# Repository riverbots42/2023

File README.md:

# 2023

# Introduction

Clearinghouse repository for all code and random files related to the Riverbot team's 2023 robot stuff.

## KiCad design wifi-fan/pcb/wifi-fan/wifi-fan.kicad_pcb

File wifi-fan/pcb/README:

Files in this directory:

600px-OPiZero_pinout.jpg - The pinout of the OrangePi Zero and what each pin is on the headers.
opi-zero-gpio-pins-768x716.png - The GPIO name (that the board knows) mapped to the one that Linux knows about.
winning-amp.jpg - The audio amplifier design I went with.
winning-pcb-rendered.jpg - The final PCB that I ordered from PCBWay (in glorious 3D).
winning-pcb-schematic.jpg - The final PCB that I ordered from PCBWay (in schematic format).

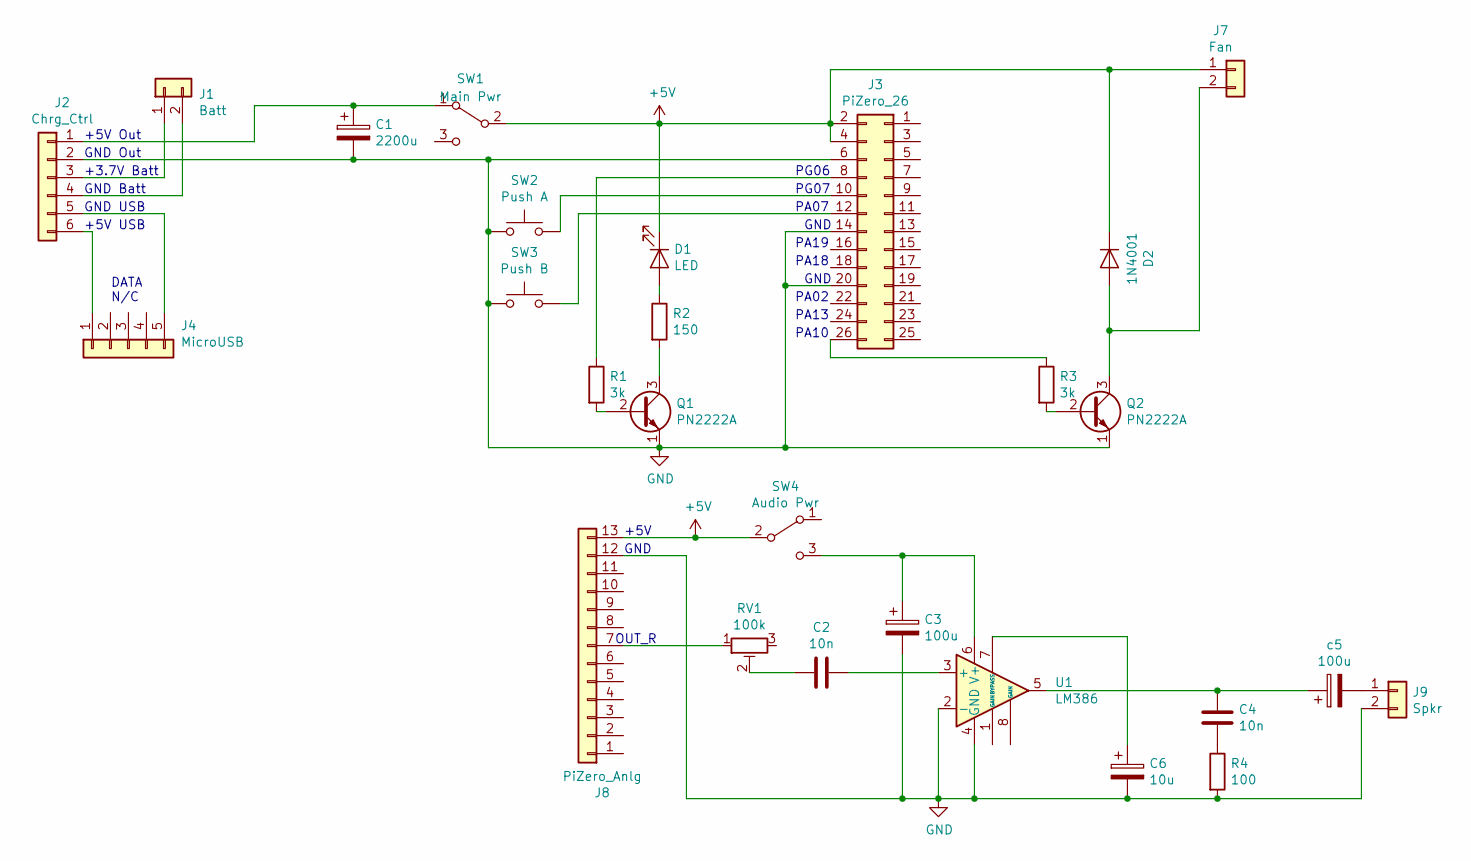
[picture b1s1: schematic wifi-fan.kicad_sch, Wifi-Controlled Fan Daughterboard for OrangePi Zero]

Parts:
C1: 2200u; CP_Radial_D10.0mm_P2.50mm
C2, C4: 10n; C_Disc_D5.0mm_W2.5mm_P2.50mm
C3: 100u; CP_Radial_D10.0mm_P2.50mm
C6: 10u; CP_Radial_D7.5mm_P2.50mm
D1: LED; LED_D5.0mm
D2: 1N4001; D_DO-41_SOD81_P10.16mm_Horizontal
J1: Batt; PinHeader_1x02_P2.54mm_Vertical
J2: Chrg_Ctrl; PinHeader_1x06_P2.54mm_Vertical
J3: PiZero_26; PinHeader_2x13_P2.54mm_Vertical
J4: MicroUSB; PinHeader_1x05_P2.54mm_Vertical
J7: Fan; PinHeader_1x02_P2.54mm_Vertical
J8: PiZero_Anlg; PinHeader_1x13_P2.54mm_Vertical
J9: Spkr; PinHeader_1x02_P2.54mm_Vertical
Q1, Q2: PN2222A; TO-92_Inline
R1, R3: 3k; R_Axial_DIN0207_L6.3mm_D2.5mm_P7.62mm_Horizontal
R2: 150; R_Axial_DIN0207_L6.3mm_D2.5mm_P7.62mm_Horizontal
R4: 100; R_Axial_DIN0207_L6.3mm_D2.5mm_P7.62mm_Horizontal
RV1: 100k; Potentiometer_Runtron_RM-065_Vertical
SW1: Main Pwr; SS12D00G3
SW2: Push A; SW_PUSH_6mm
SW3: Push B; SW_PUSH_6mm
SW4: Audio Pwr; SS12D00G3
U1: LM386; DIP-8_W7.62mm
c5: 100u; CP_Radial_D10.0mm_P2.50mm

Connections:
+5V: D1.1 (K), D2.1 (K), J3.2, J3.4, J7.1, J8.13, SW1.2 (B), SW4.2 (B); also elsewhere on the board
GND: C1.2, C3.2, C6.2, J2.2, J3.6, J3.14, J3.20, J8.12, J9.2, Q1.1 (E), Q2.1 (E), R4.2, SW2.1, SW3.1, U1.2 (-), U1.4 (GND)
unnamed 2: C1.1, J2.1, SW1.1 (A); also elsewhere on the board
unnamed: C2.1, RV1.2
unnamed: C2.2, U1.3 (+)
unnamed 5: C3.1, SW4.3 (C), U1.6 (V+); also elsewhere on the board
unnamed: C4.1, U1.5, c5.1
unnamed: C4.2, R4.1
unnamed: C6.1, U1.7 (BYPASS)
unnamed: D1.2 (A), R2.1
unnamed: D2.2 (A), J7.2, Q2.3 (C)
unnamed: J1.1, J2.3
unnamed: J1.2, J2.4
unnamed: J2.5, J4.5
unnamed: J2.6, J4.1
unnamed: J3.8, R1.1
unnamed: J3.10, SW2.2
unnamed: J3.12, SW3.2
unnamed: J3.26, R3.1
unnamed: J8.7, RV1.1
unnamed: J9.1, c5.2
unnamed: Q1.2 (B), R1.2
unnamed: Q1.3 (C), R2.2
unnamed: Q2.2 (B), R3.2

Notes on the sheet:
PA07
DATA N/C
GND
+3.7V Batt
PA13
PG07
+5V
+5V USB
GND Batt
GND Out
PA10
PA02
PA19
GND USB
OUT_R
+5V Out
PG06
PA18

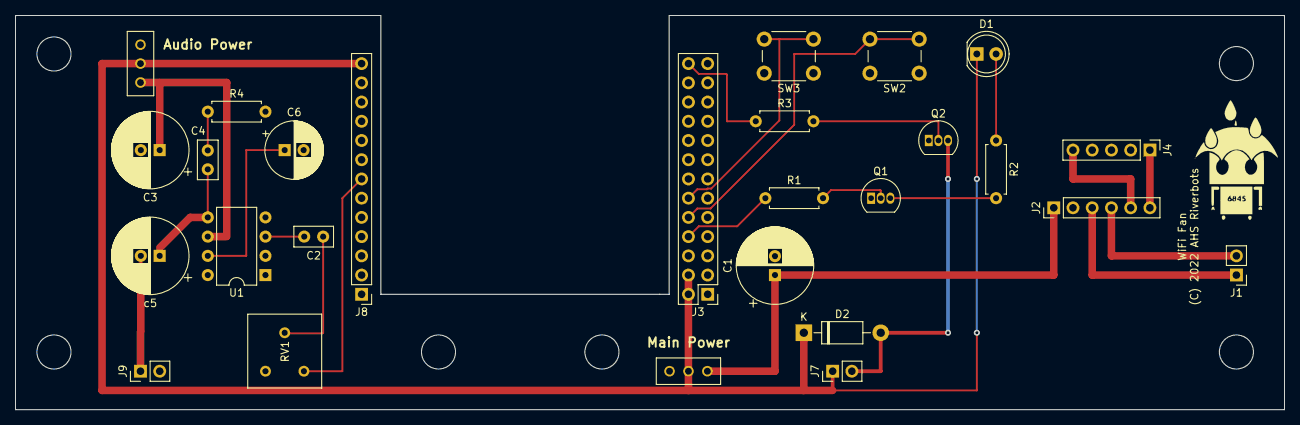
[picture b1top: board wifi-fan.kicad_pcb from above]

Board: 2 copper layers, 167.6 x 52.1 mm, 27 parts (0 on the bottom side), 24 nets.

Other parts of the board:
Audio Power: Audio Pwr; SS12D00G3
Main Power: Main Pwr; SS12D00G3

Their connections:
+5V: Audio Power.2, Main Power.2; also elsewhere on the board
unnamed 2: Main Power.1; also elsewhere on the board
unnamed 5: Audio Power.3; also elsewhere on the board

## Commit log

2022-11-03 Initial commit.
2022-11-05 Initial commit of the schematics.
2022-11-13 Add graphics.
2022-11-13 Updated to the version of the PCB BJ ordered.
2022-12-15 Initial riverbian release.
2023-01-07 Add 2023 template code from wpilib.
2023-01-07 Add beginning dox for install/download.
2023-01-08 Add test message.
2023-01-11 This is a test to see if I can commit changes
2023-01-12 hi there
2023-01-13 Fixed it.
2023-01-13 i fixed world peas
2023-01-14 Copied 2022 code for testing (On correct account)
2023-01-14 Altered 2022 code
2023-01-15 Add CTR dependencies.
2023-01-19 I've tried this
2023-01-19 please stop
2023-01-19 vITOR GONNA LOSE IT
2023-01-20 Unfinished motor control changes
2023-01-20 UnfinishedMotorControls
2023-01-21 Checking In Before I start Coding
2023-01-21 Left and Right Motor Control functionality
2023-01-21 Screw Drive Functionality
2023-01-21 Screw Drive Functionality w/ (readability) Changes
2023-01-22 Added Foundation for Use of Gyro Sensors
2023-01-25 Basics for Gyro Sensors Added & Screwdrive Power
2023-01-26 Add demo program and pointer to documentation for the gyroscope board.
2023-01-29 Built In Accelerometer and Camera Functionality
2023-02-02 Initial commit of the valentine's fundraiser stuff.
2023-02-03 Remove keys.json, which should not have been there.
2023-02-03 Add riverbots pw.
2023-02-03 Change robot WiFi AP SSID.
2023-02-03 Remove more keys, rekey stuff.
2023-02-03 Turn WPA on.
2023-02-03 Remove wayward history thingy.
2023-02-03 Resolve bug where dnsmasq could set lab.riverbots.org to localhost.
2023-02-03 Add ansible warning on the config files and additional comments on everything.
2023-02-04 Accelerometers print only on change
2023-02-04 Fix variable name.
2023-02-04 Add public-facing website including landing page.
2023-02-04 Fix CSS class, darken error color.
2023-02-04 First bits of the admin UI.
2023-02-04 Rename directory so it more accurately reflects what this one does.
2023-02-04 Add bits to build/push the docker image.
2023-02-04 Fix tag name.
2023-02-05 Added Code for New Motor Controllers
2023-02-05 WIP for the admin UI.
2023-02-06 Finish up basic admin UI; add some decent CSS, an audit UI, and QR/sticker creation.
2023-02-07 I am not done yet!
2023-02-07 Switched ScrewDrive Motor Controller to Spark
2023-02-07 WIP of send-to-printer ZPL generator.
2023-02-07 I am not done yet.
2023-02-08 Working Screw Drive and Altered Channels
2023-02-08 Screw Drive Motor Controller to Scoring Mechanism
2023-02-08 something or other
2023-02-08 Added Scew Drive Spark
2023-02-09 Add the rest of the fixed ZPL generator and something to write trivial images to the printer.
2023-02-09 Add required prereqs and update webapp to have a direct print link.
2023-02-09 Added Screw Drive Spark Foundation
2023-02-09 Add notes field.
2023-02-10 Add logging.
2023-02-10 Add dump to /tmp for debug.
2023-02-10 Re-add corrected inventory.
2023-02-10 Add one-click print via jquery.
2023-02-11 Screw Drive Functionality & Updated Comments
2023-02-11 Screw Drive To Individual Bumpers On Controller
2023-02-11 Update graphics, move graphic params to love.properties.
2023-02-12 Add monitor for robot communications.
2023-02-13 Commit a mercifully-only-25s version of the rickroll.
2023-02-14 + Cameras, speed down to 30%
2023-02-15 Made terrible change to motor control.
2023-02-17 Non-functional Autonomous
2023-02-18 Non-Functional Autonomous Files Added
2023-02-18 Non-Functional Autonomous w/ Files Added
2023-02-18 Add revised space force sticker.
2023-02-18 Autonomous Foundation Set Up
2023-02-18 Deleted Unnecessary File
2023-02-22 Deleted Previous Auto Changes
2023-02-22 Odometer Foundation
2023-02-23 Add cheat sheet.
2023-02-23 Render better on dark backgrounds.
2023-02-23 Auto Uses Encoders
2023-02-23 Add moar README.
2023-02-24 Minor Change To Readme
    I'm just being picky and noticed a slight typo
2023-02-25 Even moar cheet.
2023-02-25 Basic Encoders Function and Framework For Pathing
2023-02-25 Left and Right Encoders
2023-02-25 Left Encoder Channel Update
2023-02-25 Add gfx.
2023-02-26 Working Autonomous
2023-02-26 Working Autonomous!
2023-02-28 Cleaned Code & Stop Method
2023-02-28 Added autobalance. Needs a lot more. Needs test.
2023-03-01 Added moving average. Needs testing.
2023-03-01 Add sponsor logos in glorious black and white.
2023-03-01 Added Cameras Back
2023-03-03 Pathing presets
    Text file to quickly change code based off of starting position
    Need to clean code but in competition
2023-03-03 Competition Updates
2023-03-08 Added Nitro Button (probably X).
2023-03-09 Edited Path For Auto Balance
2023-03-09 Slight Organization
2023-03-10 Updated Motor adjustment speed
2023-03-14 Compitition Changes
2023-03-14 Removed Unused Imports
2023-03-21 Added AutoBalance as a class. Easier to use :)
2023-03-23 Added balancing to updated main. Need to integrate
2023-03-23 Edited Pathing
2023-04-06 Add changes to roll out the code on the admin website.
2023-04-06 Add README for the public website.
2023-04-06 Add dox.
2023-04-06 Moar dox.
2023-04-18 Add second wifi interface.
2023-04-25 Rm unneeded packet mangler; add 2nd wifi.
2023-04-25 Write config no matter what.
2023-10-16 Add custom image printing shortcut
2024-01-20 First part of making this app multi-year.
2024-01-21 More support for multiple years.
2024-01-24 More WIP for supporting multiple years.
2024-01-24 Finish 2023/4 year split WIP.
2024-01-26 Try to fix JSP 500 on sticker.jsp.
2024-01-26 Try to fix builds where docker is not present but podman is.
2024-01-28 Update sticker to 2.5x1.5.
2024-03-21 Add monitor thingy.
2024-10-08 Various works in progress.
2025-01-11 Various changes required by new lab server and new AHS network topology.
2025-02-08 Add 2025.
2025-02-08 Make sticker content fit better.
2025-02-08 Hopefully fix iOS.
2025-02-08 Update sticker 2.
2025-02-08 Adjust text placement.
2025-02-08 Mod sticker and whatnot.
2025-02-08 Name change of internal host.
2025-02-10 Fix for iOS.
2025-02-10 Version bump, add notification for iOS.
2025-02-10 Version bump, warning to apple users.
2025-04-19 Sync up with current hardware.
2025-04-19 Add NFT rules thingy.
2026-01-31 Add start of 2026.
2026-01-31 New laptop background.
2026-01-31 Change URL.
2026-02-04 Sync with WIP.
2026-02-07 Add new svg for background.
2026-02-07 When running from lab, use relevang fqdn.
2026-02-07 Add paid field to system.
2026-02-07 Add gfx
2026-02-07 WIP to add second sticker code, decouple dims and fields from being hardcoded.
2026-02-07 Add word wrap, layout for sticker 2.
2026-02-13 Fix sender/recipient on label.
2026-02-19 Add 2026 cart stickers.

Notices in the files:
wifi-fan/pcb/wifi-fan/wifi-fan.kicad_pcb:
(C) 2022 AHS Riverbots
